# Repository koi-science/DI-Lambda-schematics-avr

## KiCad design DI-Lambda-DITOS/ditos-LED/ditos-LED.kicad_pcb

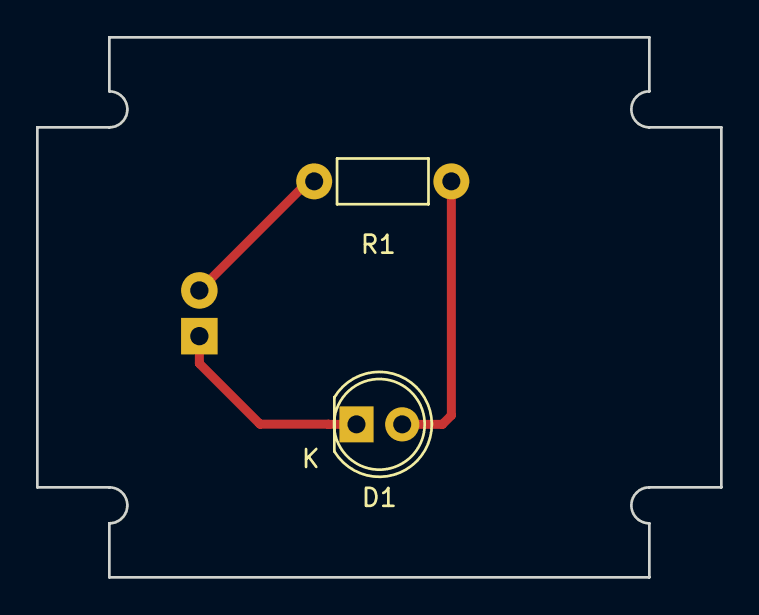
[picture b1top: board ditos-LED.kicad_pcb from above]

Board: 2 copper layers, 38.0 x 30.0 mm, 3 parts (1 on the bottom side), 3 nets.

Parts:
D1: LED; LED-5MM
P1: CONN_01X02; Pin_Header_Straight_1x02
R1: R; Resistor_Horizontal_RM7mm

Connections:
unnamed: D1.1, P1.1
unnamed: D1.2, R1.1
unnamed: P1.2, R1.2
